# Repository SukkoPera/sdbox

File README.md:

# sdbox
sdbox is a device that allows connecting an SD card to the parallel port of an Amiga computer.

## Summary
This is just my customization of [the original project by Jorgen Bilander and Niklas Ekström](https://github.com/jbilander/sdbox). I already had many of the components it needs in a different size/format and I didn't want to buy other ones, so I just changed the PCB to use those, which means:
- Use DB-25 edge connector
- Use 0805 resistors
- Use SOT-23 BJTs
- Remove the overcomplicated (IMHO) power circuit, the USB connector on the Nano is enough for me (See below)
- Lose compatibility with all existing 3D-printable enclosures

Isn't Open Hardware great?

## Usage
Please refer to [the original project](https://github.com/jbilander/sdbox) for all documentation, firmware, drivers, etc.

Note that **this board needs external power** which can be provided through the USB connector on your Nano. Choose a Nano with your favorite USB connector flavour, as you can easily find them with MiniUSB, MicroUSB and even USB-C connectors.

## Assembly
C1 is not necessary.

I also suggest NOT to install D3. If you do, please note that even though the board will appear to be powered as soon as you connect it to your Amiga, **the current provided will not be enough and it will not function correctly**. If you experience hangs, *bad number* errors or anything odd, this is likely the cause. If you are adventurous, you can modify your Amiga so that it provides unlimited current on the parallel port, but **this is dangerous and not recommended**, thus I'm not even going to explain how to perform this modification. In the recommended usage D3 has no purpose and can be skipped.

## Releases
If you want to get this board produced, you are recommended to get [the latest release](https://github.com/SukkoPera/sdbox/releases) rather than the current git version, as the latter might be under development and is not guaranteed to be working.

Every release is accompanied by its Bill Of Materials (BOM) file and any relevant notes about it, which you are recommended to read carefully.

## License
sdbox is Open Hardware released under the GNU General Public License (GPL) v3. If you make any modifications to the board, **you must** contribute them back.

sdbox is provided to you ‘as is’ and without any express or implied warranties whatsoever with respect to its functionality, operability or use, including, without limitation, any implied warranties of merchantability, fitness for a particular purpose or infringement. We expressly disclaim any liability whatsoever for any direct, indirect, consequential, incidental or special damages, including, without limitation, lost revenues, lost profits, losses resulting from business interruption or loss of data, regardless of the form of action or legal theory under which the liability may be asserted, even if advised of the possibility or likelihood of such damages.

## Thanks
- Thanks to Jorgen Bilander and Niklas Ekström for their work.
- 3D model of MicroSD module by [john](https://grabcad.com/library/sd-card-reader-4)
- 3D model of Arduino Nano by [Andrew_Whitham](https://grabcad.com/library/arduino-nano--1)

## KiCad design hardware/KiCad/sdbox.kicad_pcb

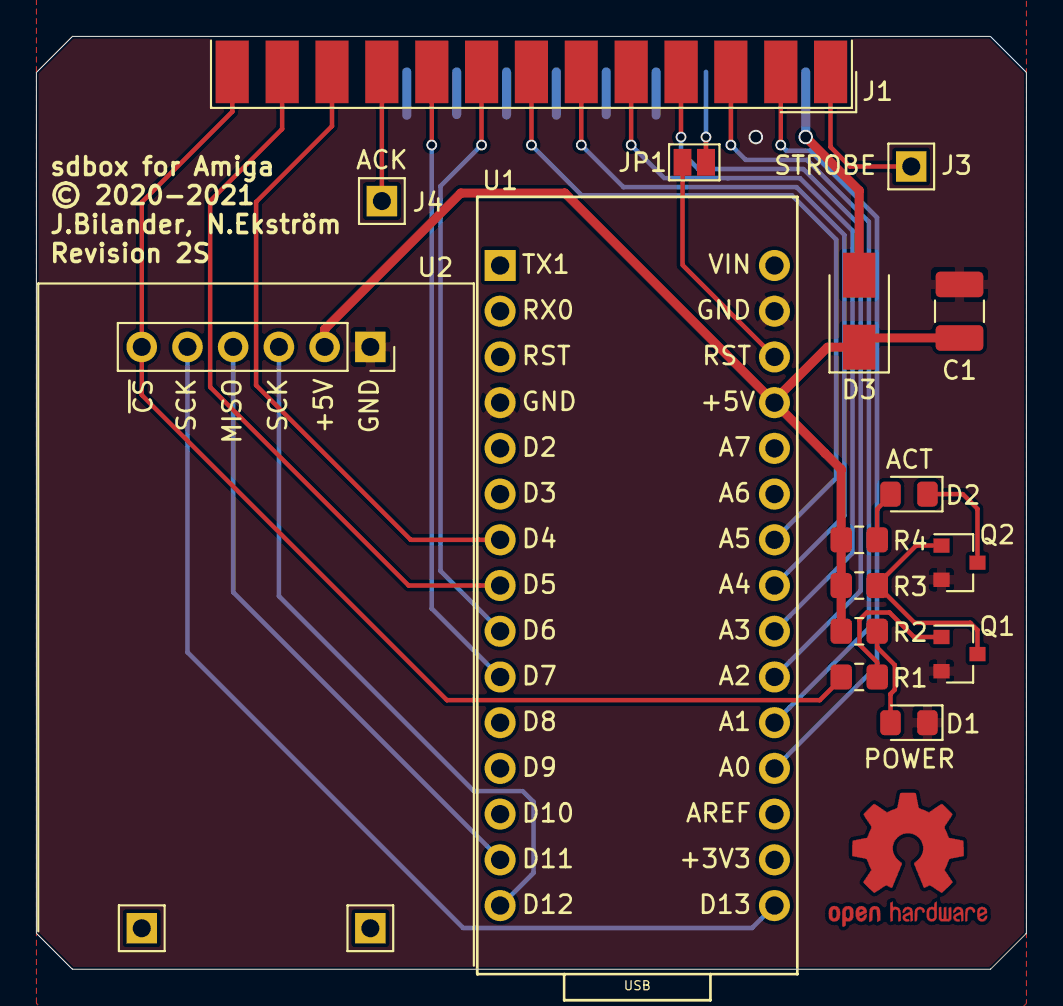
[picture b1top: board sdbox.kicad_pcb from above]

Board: 2 copper layers, 55.0 x 51.8 mm, 19 parts (0 on the bottom side), 26 nets.

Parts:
C1: 100u; C_1210_3225Metric_Pad1.42x2.65mm_HandSolder
D1: Power LED Indicator; LED_0805_2012Metric_Pad1.15x1.40mm_HandSolder
D2: Activity LED Indicator; LED_0805_2012Metric_Pad1.15x1.40mm_HandSolder
D3: 1n5819; D_SMA
J1: TO_PARALLEL_PORT; DSUB-25_Male_EdgeMount_P2.77mm
J3, J4, J5, J6: Conn_01x01; PinHeader_1x01_P2.54mm_Vertical
JP1: SolderJumper_Open; SolderJumper-2_P1.3mm_Open_Pad1.0x1.5mm
Q1, Q2: BC847BW; SOT-23
R1, R3: 4.7k; R_0805_2012Metric_Pad1.20x1.40mm_HandSolder
R2, R4: 120; R_0805_2012Metric_Pad1.20x1.40mm_HandSolder
U1: Arduino_Nano_V3; Arduino_Nano_Socket
U2: Micro_SD_Card_Module; MicroSDModule
V0: Void; OSHW-Logo2_9.8x8mm_Copper

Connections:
5V: C1.2, D3.1, R2.1, R3.1, R4.2, U1.5V, U2.2
ACK: J1.10, J4.1
Amiga5V: D3.2, J1.14
BUSY: J1.11, U1.D4
D0: J1.2, U1.A0
D1: J1.3, U1.A1
D2: J1.4, U1.A2
D3: J1.5, U1.A3
D4: J1.6, U1.A4
D5: J1.7, U1.A5
D6: J1.8, U1.D6
D7: J1.9, U1.D7
GND: C1.1, D1.1, J1.17, J1.18, J1.19, J1.20, J1.21, J1.22, Q1.2, Q2.2, U1.GND1, U1.GND2, U2.1
MISO: U1.D12, U2.3
MOSI: U1.D11, U2.4
unnamed: D1.2, R2.2
unnamed: D2.1, Q2.3
unnamed: D2.2, R4.1
unnamed: JP1.1, U1.RST2
unnamed: Q1.1, R1.1
unnamed: Q1.3, Q2.1, R3.2
POUT: J1.12, U1.D5
RESET: J1.16, JP1.2
SCK: U1.D13, U2.5
SELECT: J1.13, R1.2, U2.6
STROBE: J1.1, J3.1

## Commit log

2020-12-30 Remove barrel jack, simplify power circuit, use SMD leds, improve 3D model
2020-12-30 Switch connector to edge-mount
2020-12-31 Add ACK label
2020-12-31 Get back to protruding Nano and SD module
2020-12-31 Use SOT-23 BJTs
2020-12-31 Minor tweaks
2021-01-25 Add resistor values
2021-01-25 Add pin names on silkscreen
2021-04-11 Add renders
2021-04-11 Only keep PCB
2021-04-11 Move KiCad project to root
2021-04-11 Add credits and point upstream for everything
2021-04-11 Use better .gitignore and add missing files
2021-04-11 Add note
2021-04-11 Remove fp-info-cache

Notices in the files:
hardware/KiCad/sdbox.kicad_pcb:
© 2020-2021
